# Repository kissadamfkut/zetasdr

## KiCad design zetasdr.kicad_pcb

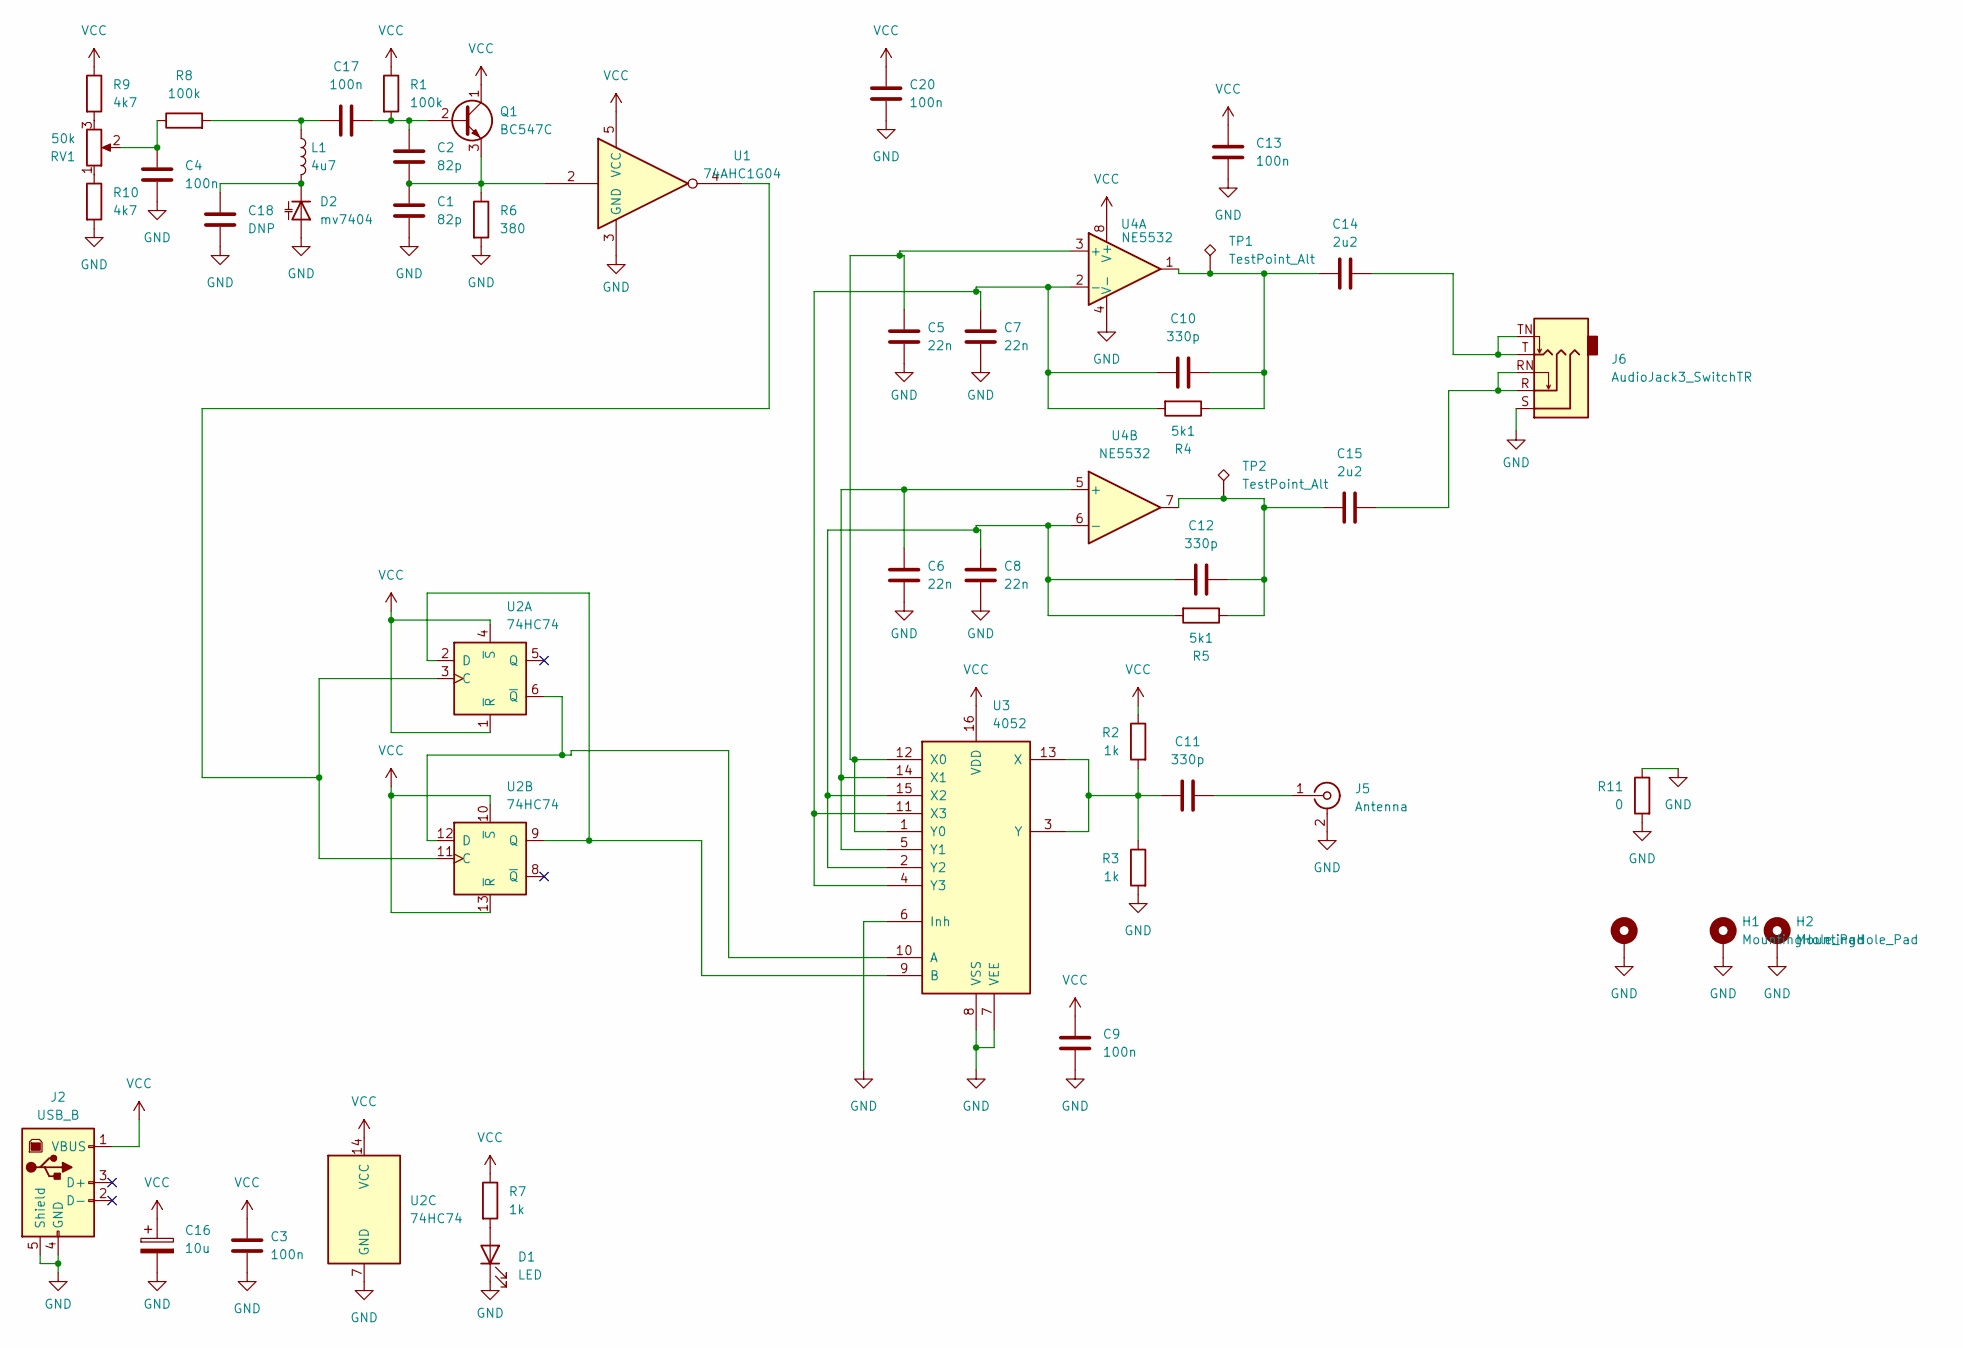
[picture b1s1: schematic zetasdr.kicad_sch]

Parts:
C1, C2: 82p; C_0805_2012Metric_Pad1.18x1.45mm_HandSolder
C3, C4, C9, C13, C17: 100n; C_0805_2012Metric_Pad1.18x1.45mm_HandSolder
C5, C6, C7, C8: 22n; C_Disc_D3.0mm_W1.6mm_P2.50mm
C10, C11, C12: 330p; C_Disc_D3.0mm_W1.6mm_P2.50mm
C14, C15: 2u2; C_0805_2012Metric_Pad1.18x1.45mm_HandSolder
C16: 10u; CP_Radial_D5.0mm_P2.50mm
C18: DNP; C_0805_2012Metric_Pad1.18x1.45mm_HandSolder
C20: 100n; C_Disc_D3.0mm_W1.6mm_P2.50mm
D1: LED; LED_D3.0mm
D2: mv7404; SOT-223-3_TabPin2
H1, H2, H4: MountingHole_Pad; MountingHole_3.2mm_M3_Pad
J2: USB_B; USB_B_Lumberg_2411_02_Horizontal
J5: Antenna; SMA_Amphenol_901-143_Horizontal
J6: AudioJack3_SwitchTR; Jack_3.5mm_CUI_SJ1-3525N_Horizontal
L1: 4u7; L_1210_3225Metric_Pad1.42x2.65mm_HandSolder
Q1: BC547C; TO-92_Inline_Wide
R1: 100k; R_Axial_DIN0204_L3.6mm_D1.6mm_P2.54mm_Vertical
R2, R3: 1k; R_Axial_DIN0204_L3.6mm_D1.6mm_P5.08mm_Horizontal
R4: 5k1; R_Axial_DIN0204_L3.6mm_D1.6mm_P2.54mm_Vertical
R5: 5k1; R_Axial_DIN0204_L3.6mm_D1.6mm_P5.08mm_Horizontal
R6: 380; R_Axial_DIN0204_L3.6mm_D1.6mm_P5.08mm_Horizontal
R7: 1k; R_0805_2012Metric_Pad1.20x1.40mm_HandSolder
R8: 100k; R_0805_2012Metric_Pad1.20x1.40mm_HandSolder
R9, R10: 4k7; R_0805_2012Metric_Pad1.20x1.40mm_HandSolder
R11: 0; R_Axial_DIN0309_L9.0mm_D3.2mm_P12.70mm_Horizontal
RV1: 50k; Potentiometer_Piher_T-16H_Single_Horizontal
TP1, TP2: TestPoint_Alt; PinSocket_1x01_P2.54mm_Vertical
U1: 74AHC1G04; SOT-23-5_HandSoldering
U2: 74HC74; DIP-14_W7.62mm_Socket_LongPads
U3: 4052; DIP-16_W7.62mm_Socket_LongPads
U4: NE5532; DIP-8_W7.62mm_Socket_LongPads

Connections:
GND: C1.2, C3.2, C4.2, C5.2, C6.2, C7.2, C8.2, C9.1, C13.1, C16.2, C18.2, C20.2, D1.1 (K), D2.1 (A), H1.1, H2.1, H4.1, J2.4 (GND), J2.5 (Shield), J5.2 (Ext), J6.S, R3.2, R6.2, R10.2, R11.1, R11.2, U1.3 (GND), U2.7 (GND), U3.6 (Inh), U3.7 (VEE), U3.8 (VSS), U4.4 (V-)
unnamed: C4.1, R8.1, RV1.2
unnamed: C10.2, C14.1, R4.1, TP1.1, U4.1
unnamed: C12.2, C15.1, R5.1, TP2.1, U4.7
unnamed: C14.2, J6.T, J6.TN
unnamed: C15.2, J6.R, J6.RN
unnamed: C17.1, L1.1, R8.2
unnamed: D1.2 (A), R7.2
unnamed: C18.1, D2.2 (K), L1.2
unnamed: C11.2, J5.1 (In)
unnamed: C2.1, C17.2, Q1.2 (B), R1.2
unnamed: C1.1, C2.2, Q1.3 (E), R6.1, U1.2
unnamed: R9.2, RV1.3
unnamed: R10.1, RV1.1
unnamed: U1.4, U2.3 (C), U2.11 (C)
unnamed: U2.2 (D), U2.9 (Q), U3.9 (B)
unnamed: U2.6 (~Q), U2.12 (D), U3.10 (A)
unnamed: C5.1, U3.1 (Y0), U3.12 (X0), U4.3 (+)
unnamed: C6.1, U3.5 (Y1), U3.14 (X1), U4.5 (+)
unnamed: C8.1, C12.1, R5.2, U3.2 (Y2), U3.15 (X2), U4.6 (-)
unnamed: C7.1, C10.1, R4.2, U3.4 (Y3), U3.11 (X3), U4.2 (-)
unnamed: C11.1, R2.2, R3.1, U3.3 (Y), U3.13 (X)
VCC: C3.1, C9.2, C13.2, C16.1, C20.1, J2.1 (VBUS), Q1.1 (C), R1.1, R2.1, R7.1, R9.1, U1.5 (VCC), U2.1 (~R), U2.4 (~S), U2.10 (~S), U2.13 (~R), U2.14 (VCC), U3.16 (VDD), U4.8 (V+)

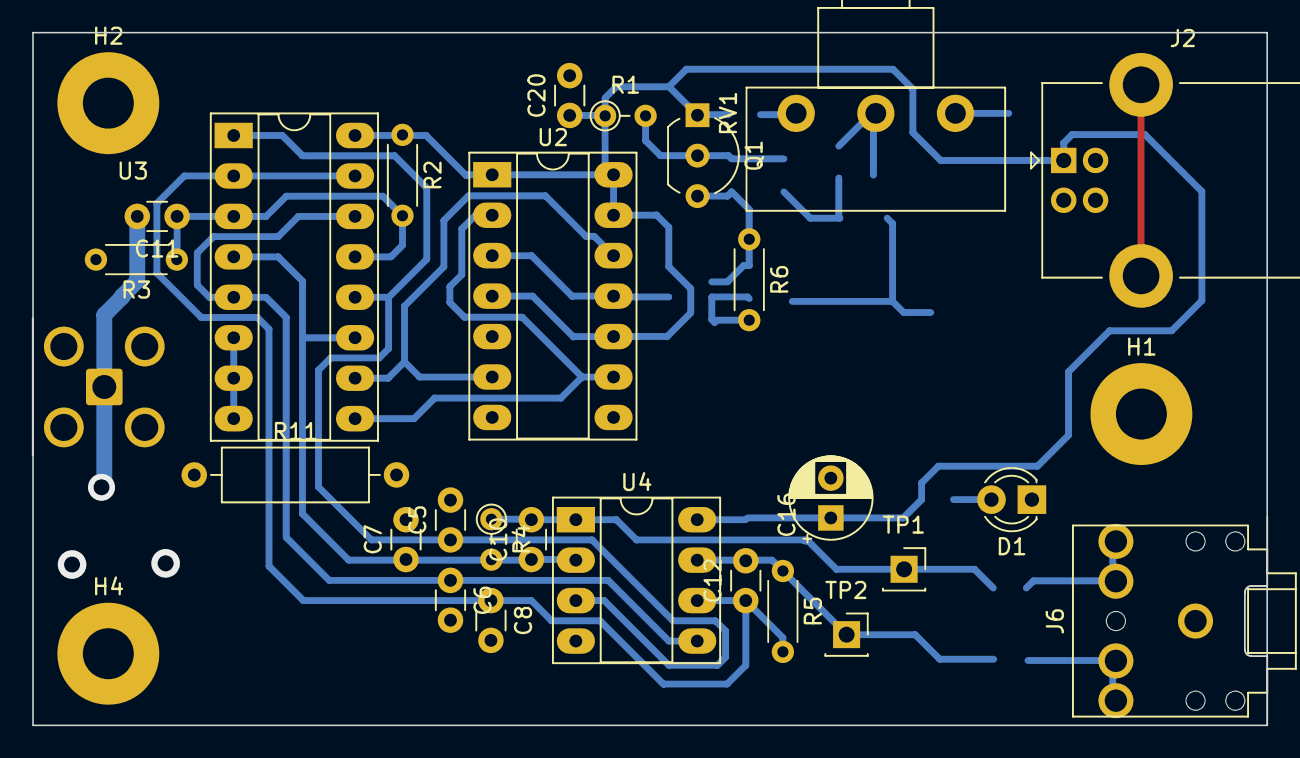
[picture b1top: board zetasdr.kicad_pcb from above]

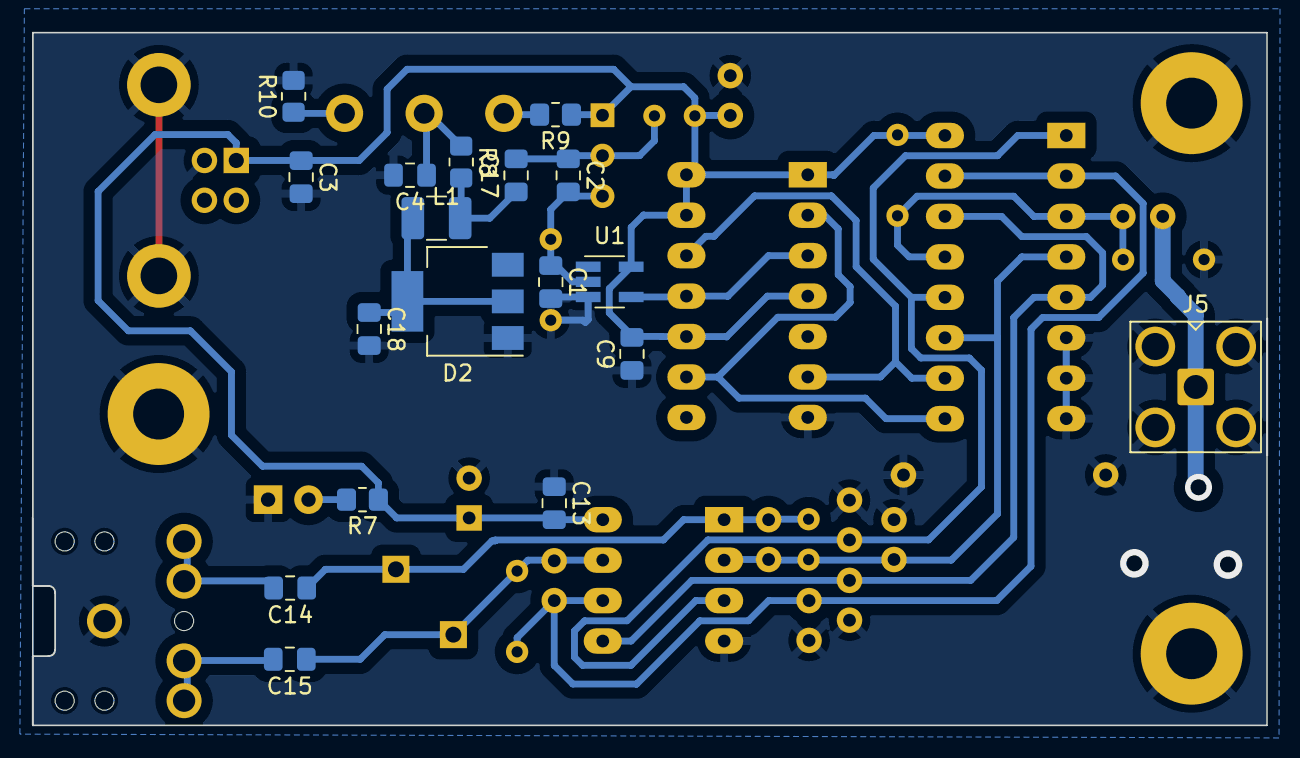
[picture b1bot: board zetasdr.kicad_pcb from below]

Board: 2 copper layers, 77.5 x 43.5 mm, 47 parts (18 on the bottom side), 23 nets.

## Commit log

2023-11-21 Initial release
2023-11-21 Add Hungarian BOM
2023-11-21 Fix bom
